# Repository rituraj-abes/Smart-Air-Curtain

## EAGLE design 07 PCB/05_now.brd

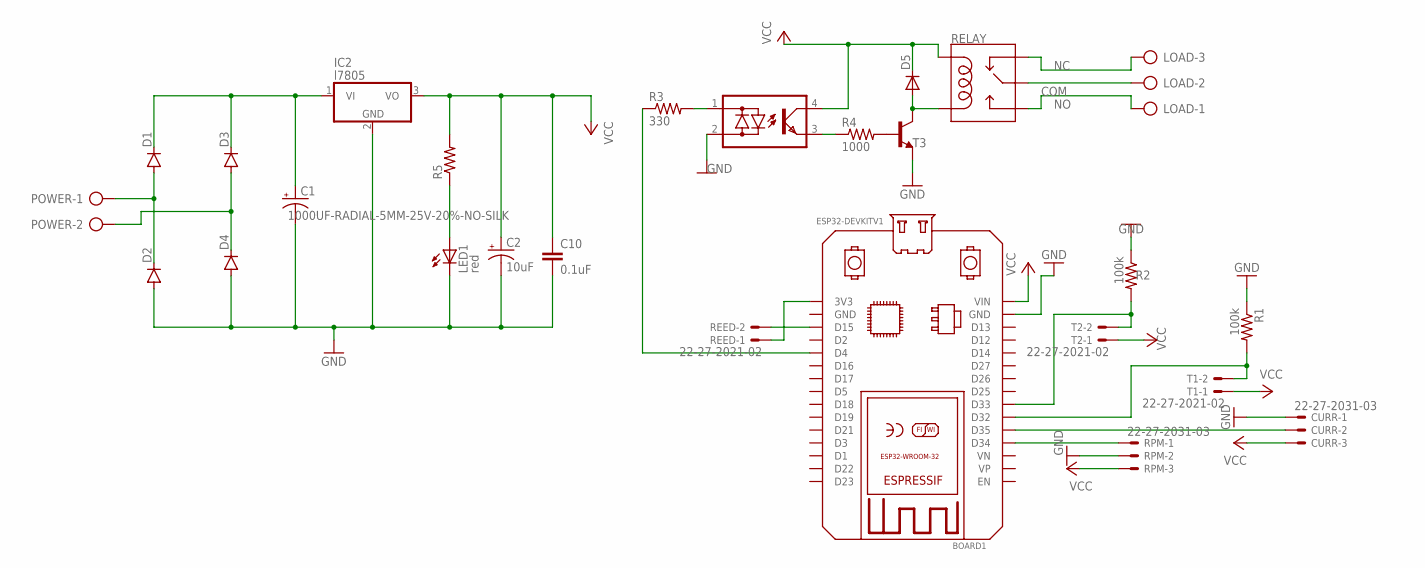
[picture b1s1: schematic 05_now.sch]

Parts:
BOARD1: ESP32DEVKITV1; ESP32-DEVKITV1
C1: 1000UF-RADIAL-5MM-25V-20%-NO-SILK; CPOL-RADIAL-5MM-10MM-NS
C2: 10uF; CPOL-RADIAL-2.5MM-5MM
C10: 0.1uF; CAP-PTH-SMALL-KIT
CURR: 22-27-2031-03; 6410-03
D1, D2, D3, D4, D5: 1N4004; DO41-10
IC2: l7805; TO220V
LED1: red; LED3MM
LOAD: AK500/3
OPTO: SFH620A; DIL04
POWER: AK500/2
R1, R2: 100k; 0204/7
R3: 330; 0204/7
R4: 1000; 0204/7
R5: R-US_0204/7; 0204/7
REED: 22-27-2021-02; 6410-02
RELAY: RELAY-SPDT; RELAY_G5LE
RPM: 22-27-2031-03; 6410-03
T1, T2: 22-27-2021-02; 6410-02
T3: BC547; TO92

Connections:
COM: LOAD.2, RELAY.1 (MAIN)
GND: BOARD1.GND, C1.-, C2.2 (-), C10.2, CURR.1, D2.A, D4.A, IC2.2 (GND), LED1.K (C), OPTO.2 (AC2), R1.1, R2.1, RPM.2, T3.1 (E)
unnamed: BOARD1.D15, REED.2
unnamed: BOARD1.3V3, REED.1
unnamed: BOARD1.D34, RPM.1
unnamed: OPTO.1 (AC1), R3.2
unnamed: BOARD1.D35, CURR.2
unnamed: BOARD1.D4, R3.1
unnamed: C1.+, D1.C, D3.C, IC2.1 (VI)
unnamed: D3.A, D4.C, POWER.2
unnamed: D1.A, D2.C, POWER.1
unnamed: BOARD1.D32, R1.2, T1.2
unnamed: OPTO.3 (E), R4.1
unnamed: R4.2, T3.2 (B)
unnamed: D5.A, RELAY.5 (COIL2), T3.3 (C)
unnamed: BOARD1.D33, R2.2, T2.2
unnamed: LED1.A, R5.1
NC: LOAD.3, RELAY.4 (NC)
NO: LOAD.1, RELAY.3 (NO)
VCC: BOARD1.VIN, C2.1 (+), C10.1, CURR.3, D5.C, IC2.3 (VO), OPTO.4 (C), R5.2, RELAY.2 (COIL1), RPM.3, T1.1, T2.1

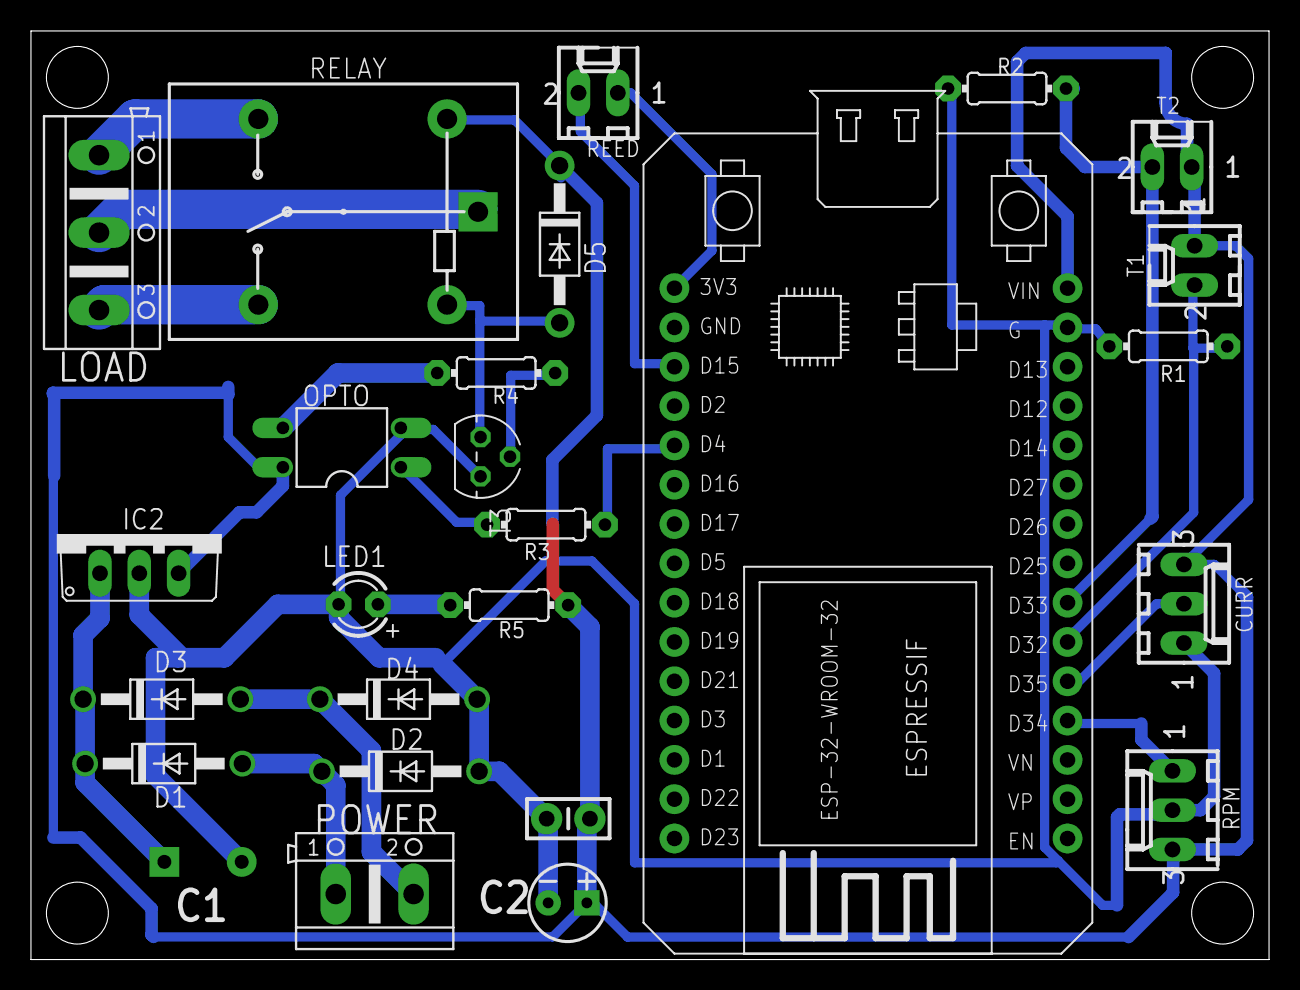
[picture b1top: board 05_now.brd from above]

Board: 2 copper layers, 80.0 x 60.0 mm, 26 parts (0 on the bottom side), 20 nets.

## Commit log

2024-07-24 Create delete.txt
    creating a folder
2024-07-24 Create 03 IR Sensor

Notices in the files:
parts and their libraries:
SparkFun-Capacitors: Licensing: Creative Commons ShareAlike 4.0 International - https://creativecommons.org/licenses/by-sa/4.0
